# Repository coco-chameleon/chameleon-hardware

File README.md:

# CoCo Chameleon

The CoCo Chameleon is a cartridge for the Tandy TRS-80 Color Computer
line of home computers from the 1980s which emulates other cartridges.
It supports all three versions of the CoCo and should be able to
replicate the computer-facing behavior of nearly any other cartridge.

The primary aim of the project is to emulate ROM cartridges and all
of the common floppy and hard disk controller cartridges from image
files stored on a MicroSD card.

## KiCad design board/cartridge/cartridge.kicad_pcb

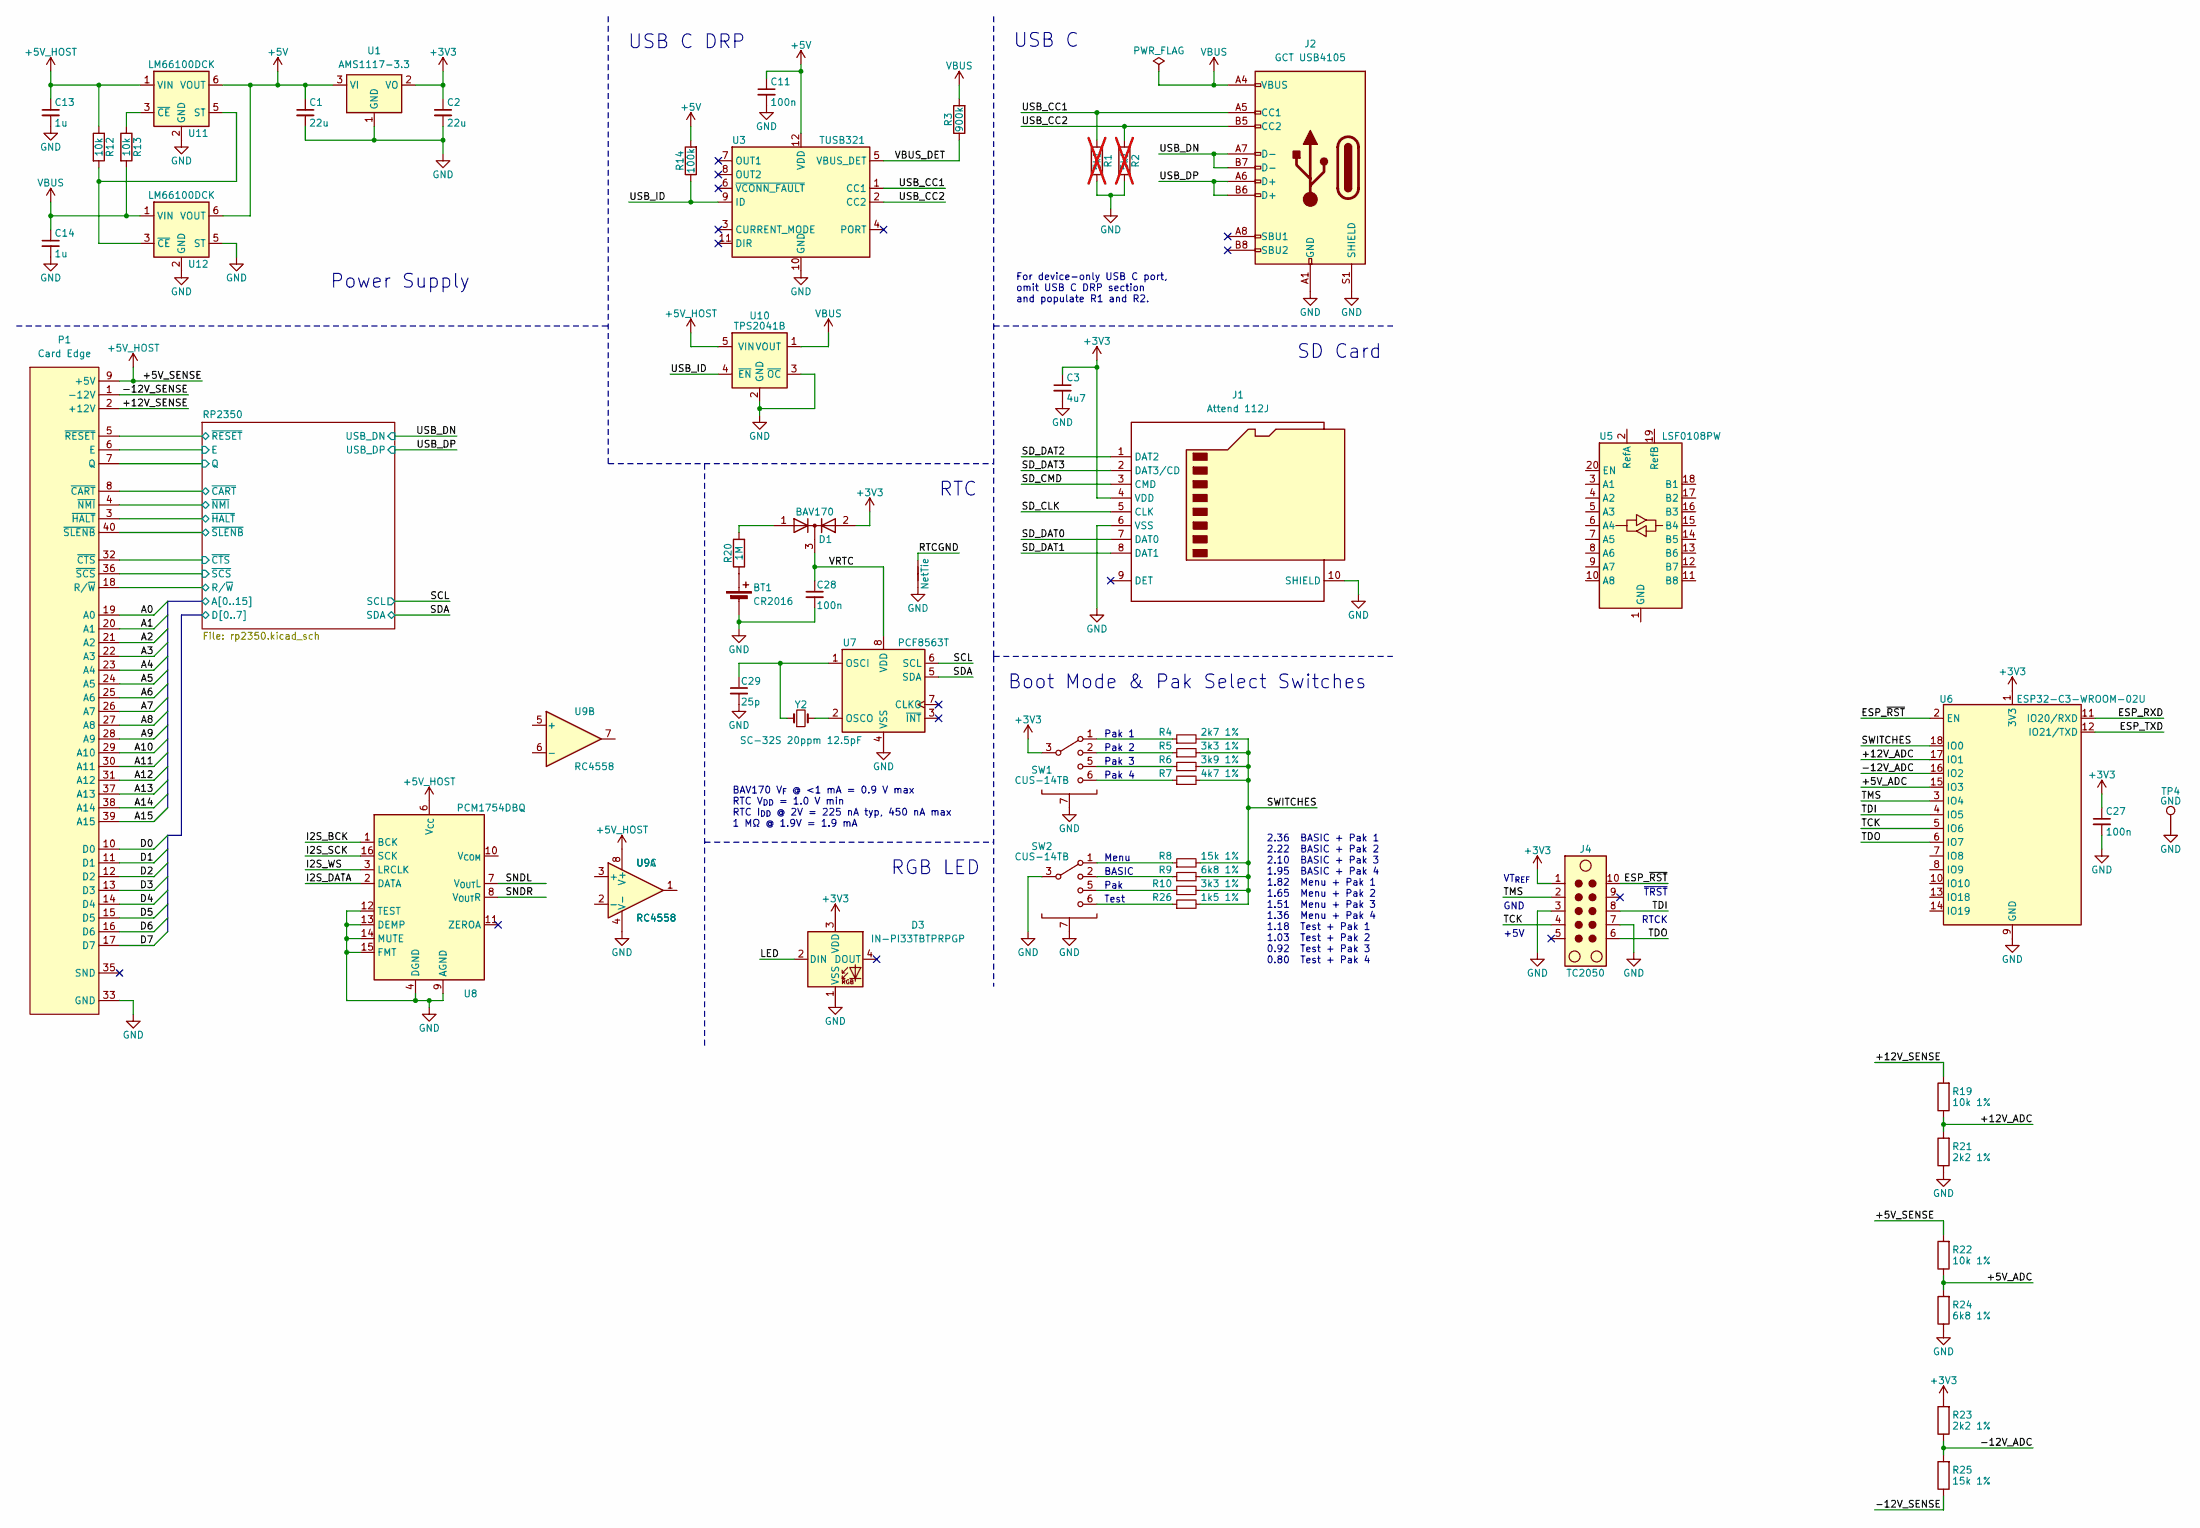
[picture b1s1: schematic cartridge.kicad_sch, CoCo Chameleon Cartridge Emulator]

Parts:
BT1: CR2016; BatteryHolder_Keystone_3026_1x2016
C1, C2: 22u; C_1206_3216Metric
C3: 4u7; C_0603_1608Metric
C11, C27, C28: 100n; C_0603_1608Metric
C13, C14: 1u; C_0603_1608Metric
C29: 25p; C_0603_1608Metric
D1: BAV170; SOT-23; LCSC C109309
D3: IN-PI33TBTPRPGP; LED_1414_3535Metric; LCSC C5259062
J1: Attend 112J; Attend_112J; LCSC C393941
J2: GCT USB4105; GCT_USB4105; LCSC C2894898
J4: TC2050; Tag-Connect_TC2050-IDC-NL_2x05_P1.27mm_Vertical
NT1: NetTie
P1: Card Edge; CoCo_Cart
R1, R2: 5k1; R_0603_1608Metric; not fitted
R3: 900k; R_0603_1608Metric
R4: 2k7 1%; R_0402_1005Metric
R5, R10: 3k3 1%; R_0402_1005Metric
R6: 3k9 1%; R_0402_1005Metric
R7: 4k7 1%; R_0402_1005Metric
R8, R25: 15k 1%; R_0402_1005Metric
R9, R24: 6k8 1%; R_0402_1005Metric
R12, R13: 10k; R_0603_1608Metric
R14: 100k; R_0603_1608Metric
R19, R22: 10k 1%; R_0402_1005Metric
R20: 1M; R_0603_1608Metric
R21, R23: 2k2 1%; R_0402_1005Metric
R26: 1k5 1%; R_0402_1005Metric
SW1, SW2: CUS-14TB; Nidec_CUS-14TB; LCSC C145846
TP4: GND; TestPoint_Pad_4.0x4.0mm
U1: AMS1117-3.3; SOT-223-3_TabPin2; LCSC C6186
U3: TUSB321; Texas_X2QFN-12_1.6x1.6mm_P0.4mm; LCSC C139392
U5: LSF0108PW; TSSOP-20_4.4x6.5mm_P0.65mm; LCSC C190219
U6: ESP32-C3-WROOM-02U
U7: PCF8563T; SOIC-8_3.9x4.9mm_P1.27mm; LCSC C7440
U8: PCM1754DBQ; SSOP-16_3.9x4.9mm_P0.635mm
U9: RC4558; SOIC-8_3.9x4.9mm_P1.27mm
U10: TPS2041B; SOT-23-5; LCSC C51386
U11, U12: LM66100DCK; SOT-363_SC-70-6; LCSC C2869734
Y2: SC-32S 20ppm 12.5pF; Crystal_SMD_3215-2Pin_3.2x1.5mm; LCSC C97606

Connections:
+3V3: C2.1, C3.1, C27.1, D1.2 (A), D3.3 (VDD), J1.4 (VDD), J4.1, R23.2, SW1.3 (COM), SW1.4 (COM), U1.2 (VO), U6.1 (3V3); also elsewhere on the board
+5V: C1.1, C11.1, R14.2, U1.3 (VI), U3.12 (VDD), U11.6 (VOUT), U12.6 (VOUT)
+5V_HOST: C13.1, P1.9 (+5V), R12.1, R22.2, U8.6 (V_{CC}), U9.8 (V+), U10.5 (VIN), U11.1 (VIN)
/+5V_ADC: R22.1, R24.2, U6.15 (IO3)
/+12V_ADC: R19.1, R21.2, U6.17 (IO1)
/+12V_SENSE: P1.2 (+12V), R19.2
/-12V_ADC: R23.1, R25.2, U6.16 (IO2)
/-12V_SENSE: P1.1 (-12V), R25.1
/ESP_RXD: U6.11 (IO20/RXD)
/ESP_TXD: U6.12 (IO21/TXD)
/ESP_~RST: J4.10, U6.2 (EN)
/I2S_BCK: U8.1 (BCK)
/I2S_DATA: U8.2 (DATA)
/I2S_SCK: U8.16 (SCK)
/I2S_WS: U8.3 (LRCLK)
/LED: D3.2 (DIN)
/RP2350/A0: P1.19 (A0); also elsewhere on the board
/RP2350/A1: P1.20 (A1); also elsewhere on the board
/RP2350/A2: P1.21 (A2); also elsewhere on the board
/RP2350/A3: P1.22 (A3); also elsewhere on the board
/RP2350/A4: P1.23 (A4); also elsewhere on the board
/RP2350/A5: P1.24 (A5); also elsewhere on the board
/RP2350/A6: P1.25 (A6); also elsewhere on the board
/RP2350/A7: P1.26 (A7); also elsewhere on the board
/RP2350/A8: P1.27 (A8); also elsewhere on the board
/RP2350/A9: P1.28 (A9); also elsewhere on the board
/RP2350/A10: P1.29 (A10); also elsewhere on the board
/RP2350/A11: P1.30 (A11); also elsewhere on the board
/RP2350/A12: P1.31 (A12); also elsewhere on the board
/RP2350/A13: P1.37 (A13); also elsewhere on the board
/RP2350/A14: P1.38 (A14); also elsewhere on the board
/RP2350/A15: P1.39 (A15); also elsewhere on the board
/RP2350/D0: P1.10 (D0); also elsewhere on the board
/RP2350/D1: P1.11 (D1); also elsewhere on the board
/RP2350/D2: P1.12 (D2); also elsewhere on the board
/RP2350/D3: P1.13 (D3); also elsewhere on the board
/RP2350/D4: P1.14 (D4); also elsewhere on the board
/RP2350/D5: P1.15 (D5); also elsewhere on the board
/RP2350/D6: P1.16 (D6); also elsewhere on the board
/RP2350/D7: P1.17 (D7); also elsewhere on the board
/RP2350/E: P1.6 (E); also elsewhere on the board
/RP2350/Q: P1.7 (Q); also elsewhere on the board
/RP2350/R/~W: P1.18 (R/~W); also elsewhere on the board
/RP2350/~CART: P1.8 (~CART); also elsewhere on the board
/RP2350/~CTS: P1.32 (~CTS); also elsewhere on the board
/RP2350/~HALT: P1.3 (~HALT); also elsewhere on the board
/RP2350/~NMI: P1.4 (~NMI); also elsewhere on the board
/RP2350/~RESET: P1.5 (~RESET); also elsewhere on the board
/RP2350/~SCS: P1.36 (~SCS); also elsewhere on the board
/RP2350/~SLENB: P1.40 (~SLENB); also elsewhere on the board
/SCL: U7.6 (SCL); also elsewhere on the board
/SDA: U7.5 (SDA); also elsewhere on the board
/SD_CLK: J1.5 (CLK)
/SD_CMD: J1.3 (CMD)
/SD_DAT0: J1.7 (DAT0)
/SD_DAT1: J1.8 (DAT1)
/SD_DAT2: J1.1 (DAT2)
/SD_DAT3: J1.2 (DAT3/CD)
/SNDL: U8.7 (V_{OUT}L)
/SNDR: U8.8 (V_{OUT}R)
/SWITCHES: R4.2, R5.2, R6.2, R7.2, R8.2, R9.2, R10.2, R26.2, U6.18 (IO0)
/TCK: J4.4, U6.5 (IO6)
/TDI: J4.8, U6.4 (IO5)
/TDO: J4.6, U6.6 (IO7)
/TMS: J4.2, U6.3 (IO4)
/USB_CC1: J2.A5 (CC1), R1.1, U3.1 (CC1)
/USB_CC2: J2.B5 (CC2), R2.1, U3.2 (CC2)
/USB_DN: J2.A7 (D-), J2.B7 (D-); also elsewhere on the board
/USB_DP: J2.A6 (D+), J2.B6 (D+); also elsewhere on the board
/USB_ID: R14.1, U3.9 (ID), U10.4 (~EN)
/VBUS_DET: R3.1, U3.5 (VBUS_DET)
/VRTC: C28.1, D1.3 (K), U7.8 (VDD)
GND: BT1.2 (-), C1.2, C2.2, C3.2, C11.2, C13.2, C14.2, C27.2, C28.2, C29.2, D3.1 (VSS), J1.6 (VSS), J1.10 (SHIELD), J2.A1 (GND), J2.A12 (GND), J2.B1 (GND), J2.B12 (GND), J2.S1 (SHIELD), J4.3, J4.7, NT1.1, P1.33 (GND), P1.34 (GND), R1.2, R2.2, R21.1, R24.1, SW1.7 (SHIELD), SW2.3 (COM), SW2.4 (COM), SW2.7 (SHIELD), TP4.1, U1.1 (GND), U3.10 (GND), U6.9 (GND), U6.19 (GND), U7.4 (VSS), U8.4 (DGND), U8.9 (AGND), U8.12 (TEST), U8.13 (DEMP), U8.14 (MUTE), U8.15 (FMT), U9.4 (V-), U10.2 (GND), U10.3 (~OC), U11.2 (GND), U12.2 (GND), U12.5 (ST); also elsewhere on the board
unnamed: BT1.1 (+), R20.1
unnamed: D1.1 (A), R20.2
unnamed: R4.1, SW1.1
unnamed: R5.1, SW1.2
unnamed: R8.1, SW2.1
unnamed: R9.1, SW2.2
unnamed: R6.1, SW1.5 (3)
unnamed: R7.1, SW1.6 (4)
unnamed: R10.1, SW2.5 (3)
unnamed: R26.1, SW2.6 (4)
unnamed: C29.1, U7.1 (OSCI), Y2.1
unnamed: U7.2 (OSCO), Y2.2
unnamed: R12.2, U11.5 (ST), U12.3 (~CE)
unnamed: R13.1, U11.3 (~CE)
VBUS: C14.1, J2.A4 (VBUS), J2.A9 (VBUS), J2.B4 (VBUS), J2.B9 (VBUS), R3.2, R13.2, U10.1 (VOUT), U12.1 (VIN)

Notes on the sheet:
SD Card
For device-only USB C port, omit USB C DRP section and populate R1 and R2.
Pak
Pak 3
BASIC
RTC
RTCK
2.36 BASIC + Pak 1 2.22 BASIC + Pak 2 2.10 BASIC + Pak 3 1.95 BASIC + Pak 4 1.82 Menu + Pak 1 1.65 Menu + Pak 2 1.51 Menu + Pak 3 1.36 Menu + Pak 4 1.18 Test + Pak 1 1.03 Test + Pak 2 0.92 Test + Pak 3 0.80 Test + Pak 4
Boot Mode & Pak Select Switches
VT_{REF}
+5V
Power Supply
BAV170 V_{F} @ <1 mA = 0.9 V max RTC V_{DD} = 1.0 V min RTC I_{DD} @ 2V = 225 nA typ, 450 nA max 1 MΩ @ 1.9V = 1.9 mA
USB C DRP
Test
~{TRST}
GND
Pak 4
Pak 1
RGB LED
Menu
Pak 2
USB C

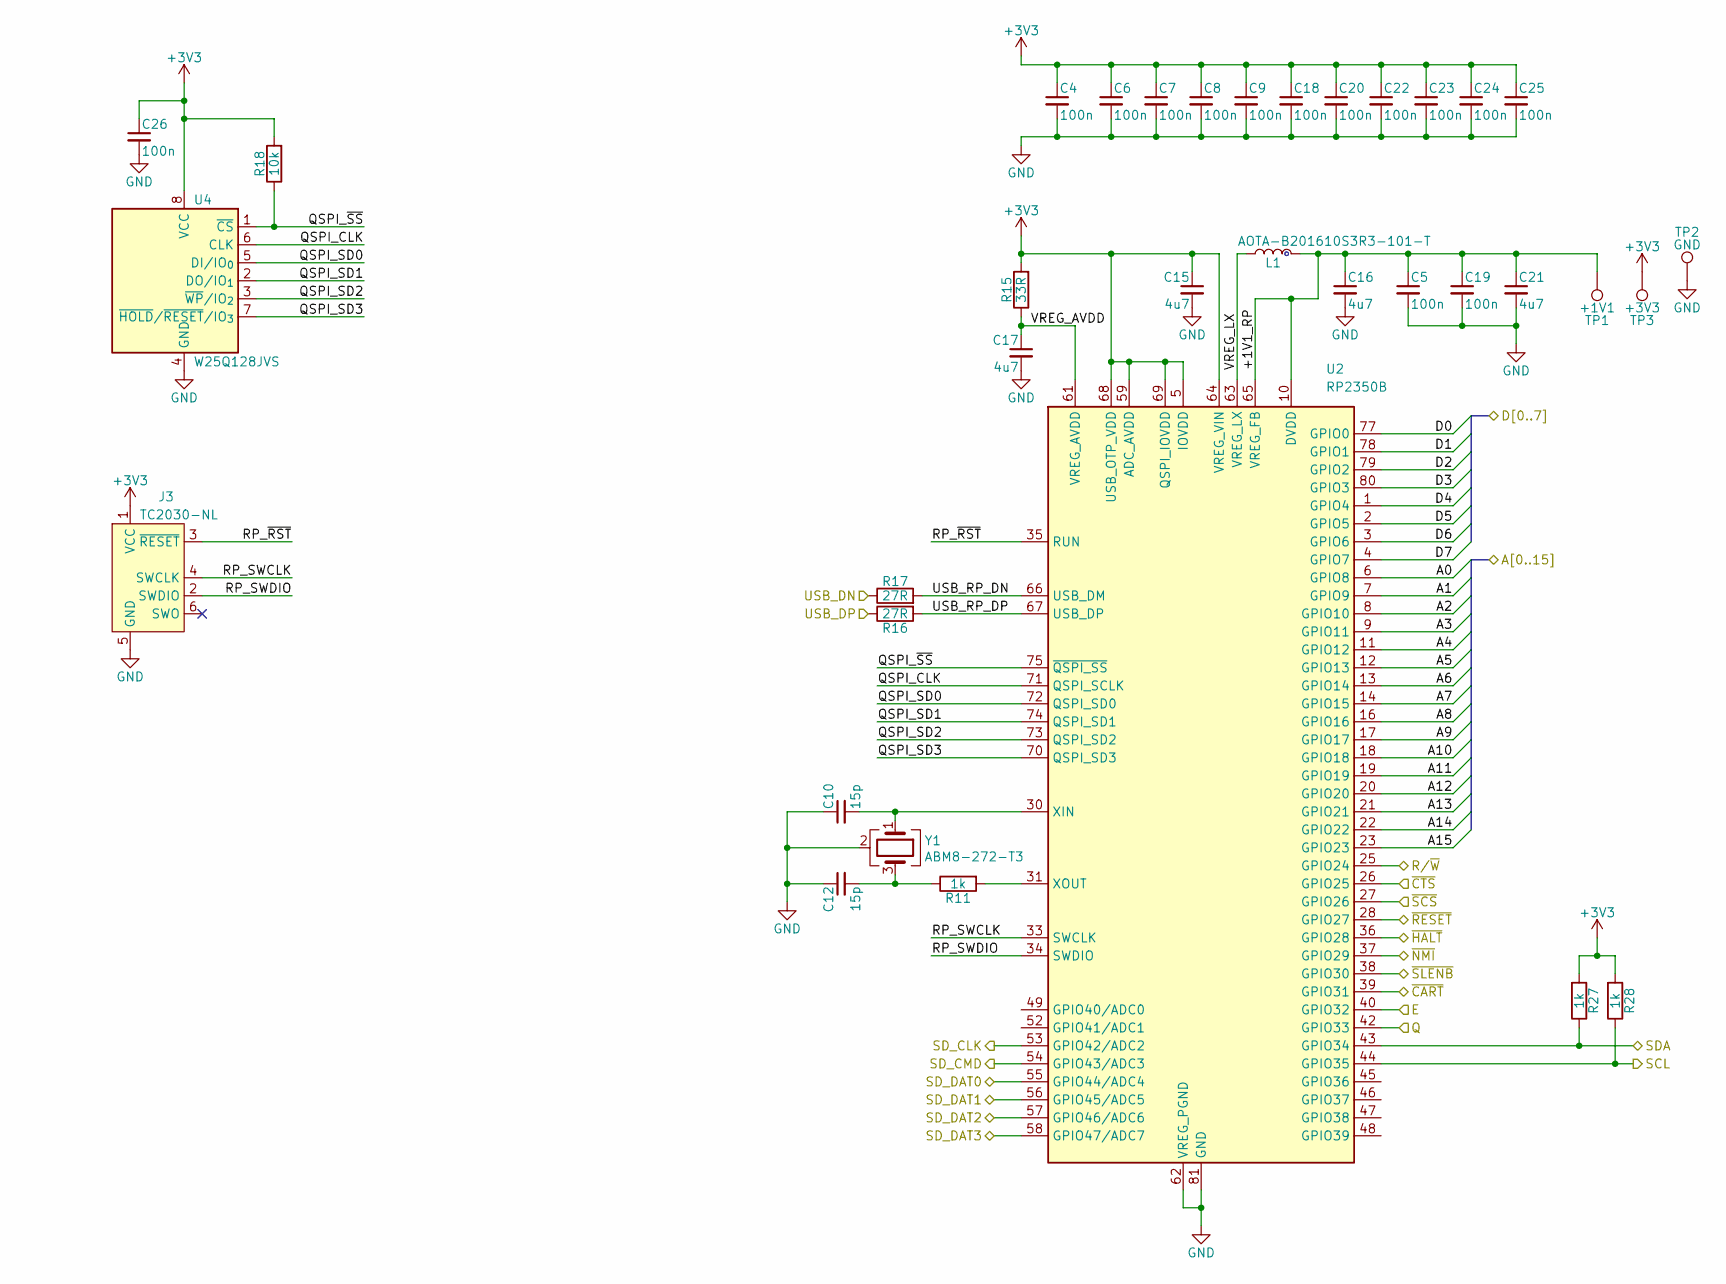
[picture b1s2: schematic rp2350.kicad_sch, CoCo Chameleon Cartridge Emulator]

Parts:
C4, C5, C6, C7, C8, C9, C18, C19, C20, C22, C23, C24, C25, C26: 100n; C_0402_1005Metric
C10, C12: 15p; C_0402_1005Metric
C15, C16: 4u7; C_0402_1005Metric_Pad0.53x0.47mm_Passthrough
C17, C21: 4u7; C_0402_1005Metric
J3: TC2030-NL; Tag-Connect_TC2030-IDC-NL_2x03_P1.27mm_Vertical
L1: AOTA-B201610S3R3-101-T; L_Polarized_2016; LCSC C42411119
R11, R27, R28: 1k; R_0402_1005Metric
R15: 33R; R_0402_1005Metric
R16, R17: 27R; R_0402_1005Metric
R18: 10k; R_0402_1005Metric
TP1: +1V1; TestPoint_Pad_D2.0mm
TP2: GND; TestPoint_Pad_4.0x4.0mm
TP3: +3V3; TestPoint_Pad_D2.0mm
U2: RP2350B; RP2350-QFN-80-1EP_10x10_P0.4mm_EP3.4x3.4mm_ThermalVias; LCSC C42415655
U4: W25Q128JVS; SOIC-8_3.9-5.3x5.3mm_P1.27mm
Y1: ABM8-272-T3; Crystal_SMD_3225-4Pin_3.2x2.5mm; LCSC C20625731

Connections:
+3V3: C4.1, C6.1, C7.1, C8.1, C9.1, C15.1, C18.1, C20.1, C22.1, C23.1, C24.1, C25.1, C26.1, J3.1 (VCC), R15.2, R18.2, R27.2, R28.2, TP3.1, U2.5 (IOVDD), U2.15 (IOVDD), U2.24 (IOVDD), U2.29 (IOVDD), U2.41 (IOVDD), U2.50 (IOVDD), U2.59 (ADC_AVDD), U2.60 (IOVDD), U2.64 (VREG_VIN), U2.68 (USB_OTP_VDD), U2.69 (QSPI_IOVDD), U2.76 (IOVDD), U4.8 (VCC); also elsewhere on the board
/RP2350/+1V1_RP: C5.1, C16.1, C19.1, C21.1, L1.1, TP1.1, U2.10 (DVDD), U2.32 (DVDD), U2.51 (DVDD), U2.65 (VREG_FB)
/RP2350/A0: U2.6 (GPIO8); also elsewhere on the board
/RP2350/A1: U2.7 (GPIO9); also elsewhere on the board
/RP2350/A2: U2.8 (GPIO10); also elsewhere on the board
/RP2350/A3: U2.9 (GPIO11); also elsewhere on the board
/RP2350/A4: U2.11 (GPIO12); also elsewhere on the board
/RP2350/A5: U2.12 (GPIO13); also elsewhere on the board
/RP2350/A6: U2.13 (GPIO14); also elsewhere on the board
/RP2350/A7: U2.14 (GPIO15); also elsewhere on the board
/RP2350/A8: U2.16 (GPIO16); also elsewhere on the board
/RP2350/A9: U2.17 (GPIO17); also elsewhere on the board
/RP2350/A10: U2.18 (GPIO18); also elsewhere on the board
/RP2350/A11: U2.19 (GPIO19); also elsewhere on the board
/RP2350/A12: U2.20 (GPIO20); also elsewhere on the board
/RP2350/A13: U2.21 (GPIO21); also elsewhere on the board
/RP2350/A14: U2.22 (GPIO22); also elsewhere on the board
/RP2350/A15: U2.23 (GPIO23); also elsewhere on the board
/RP2350/D0: U2.77 (GPIO0); also elsewhere on the board
/RP2350/D1: U2.78 (GPIO1); also elsewhere on the board
/RP2350/D2: U2.79 (GPIO2); also elsewhere on the board
/RP2350/D3: U2.80 (GPIO3); also elsewhere on the board
/RP2350/D4: U2.1 (GPIO4); also elsewhere on the board
/RP2350/D5: U2.2 (GPIO5); also elsewhere on the board
/RP2350/D6: U2.3 (GPIO6); also elsewhere on the board
/RP2350/D7: U2.4 (GPIO7); also elsewhere on the board
/RP2350/E: U2.40 (GPIO32); also elsewhere on the board
/RP2350/Q: U2.42 (GPIO33); also elsewhere on the board
/RP2350/QSPI_CLK: U2.71 (QSPI_SCLK), U4.6 (CLK)
/RP2350/QSPI_SD0: U2.72 (QSPI_SD0), U4.5 (DI/IO_{0})
/RP2350/QSPI_SD1: U2.74 (QSPI_SD1), U4.2 (DO/IO_{1})
/RP2350/QSPI_SD2: U2.73 (QSPI_SD2), U4.3 (~WP/IO_{2})
/RP2350/QSPI_SD3: U2.70 (QSPI_SD3), U4.7 (~HOLD/~RESET/IO_{3})
/RP2350/QSPI_~SS: R18.1, U2.75 (~QSPI_SS), U4.1 (~CS)
/RP2350/RP_SWCLK: J3.4 (SWCLK), U2.33 (SWCLK)
/RP2350/RP_SWDIO: J3.2 (SWDIO), U2.34 (SWDIO)
/RP2350/RP_~RST: J3.3 (~RESET), U2.35 (RUN)
/RP2350/R/~W: U2.25 (GPIO24); also elsewhere on the board
/RP2350/SD_CLK: U2.53 (GPIO42/ADC2)
/RP2350/SD_CMD: U2.54 (GPIO43/ADC3)
/RP2350/SD_DAT0: U2.55 (GPIO44/ADC4)
/RP2350/SD_DAT1: U2.56 (GPIO45/ADC5)
/RP2350/SD_DAT2: U2.57 (GPIO46/ADC6)
/RP2350/SD_DAT3: U2.58 (GPIO47/ADC7)
/RP2350/USB_RP_DN: R17.2, U2.66 (USB_DM)
/RP2350/USB_RP_DP: R16.2, U2.67 (USB_DP)
/RP2350/VREG_AVDD: C17.1, R15.1, U2.61 (VREG_AVDD)
/RP2350/VREG_LX: L1.2, U2.63 (VREG_LX)
/RP2350/~CART: U2.39 (GPIO31); also elsewhere on the board
/RP2350/~CTS: U2.26 (GPIO25); also elsewhere on the board
/RP2350/~HALT: U2.36 (GPIO28); also elsewhere on the board
/RP2350/~NMI: U2.37 (GPIO29); also elsewhere on the board
/RP2350/~RESET: U2.28 (GPIO27); also elsewhere on the board
/RP2350/~SCS: U2.27 (GPIO26); also elsewhere on the board
/RP2350/~SLENB: U2.38 (GPIO30); also elsewhere on the board
/SCL: R28.1, U2.44 (GPIO35); also elsewhere on the board
/SDA: R27.1, U2.43 (GPIO34); also elsewhere on the board
/USB_DN: R17.1; also elsewhere on the board
/USB_DP: R16.1; also elsewhere on the board
GND: C4.2, C5.2, C6.2, C7.2, C8.2, C9.2, C10.1, C12.1, C15.2, C16.2, C17.2, C18.2, C19.2, C20.2, C21.2, C22.2, C23.2, C24.2, C25.2, C26.2, J3.5 (GND), TP2.1, U2.62 (VREG_PGND), U2.81 (GND), U4.4 (GND), Y1.2 (G), Y1.4 (G); also elsewhere on the board
unnamed: C12.2, R11.1, Y1.3
unnamed: C10.2, U2.30 (XIN), Y1.1
unnamed: R11.2, U2.31 (XOUT)

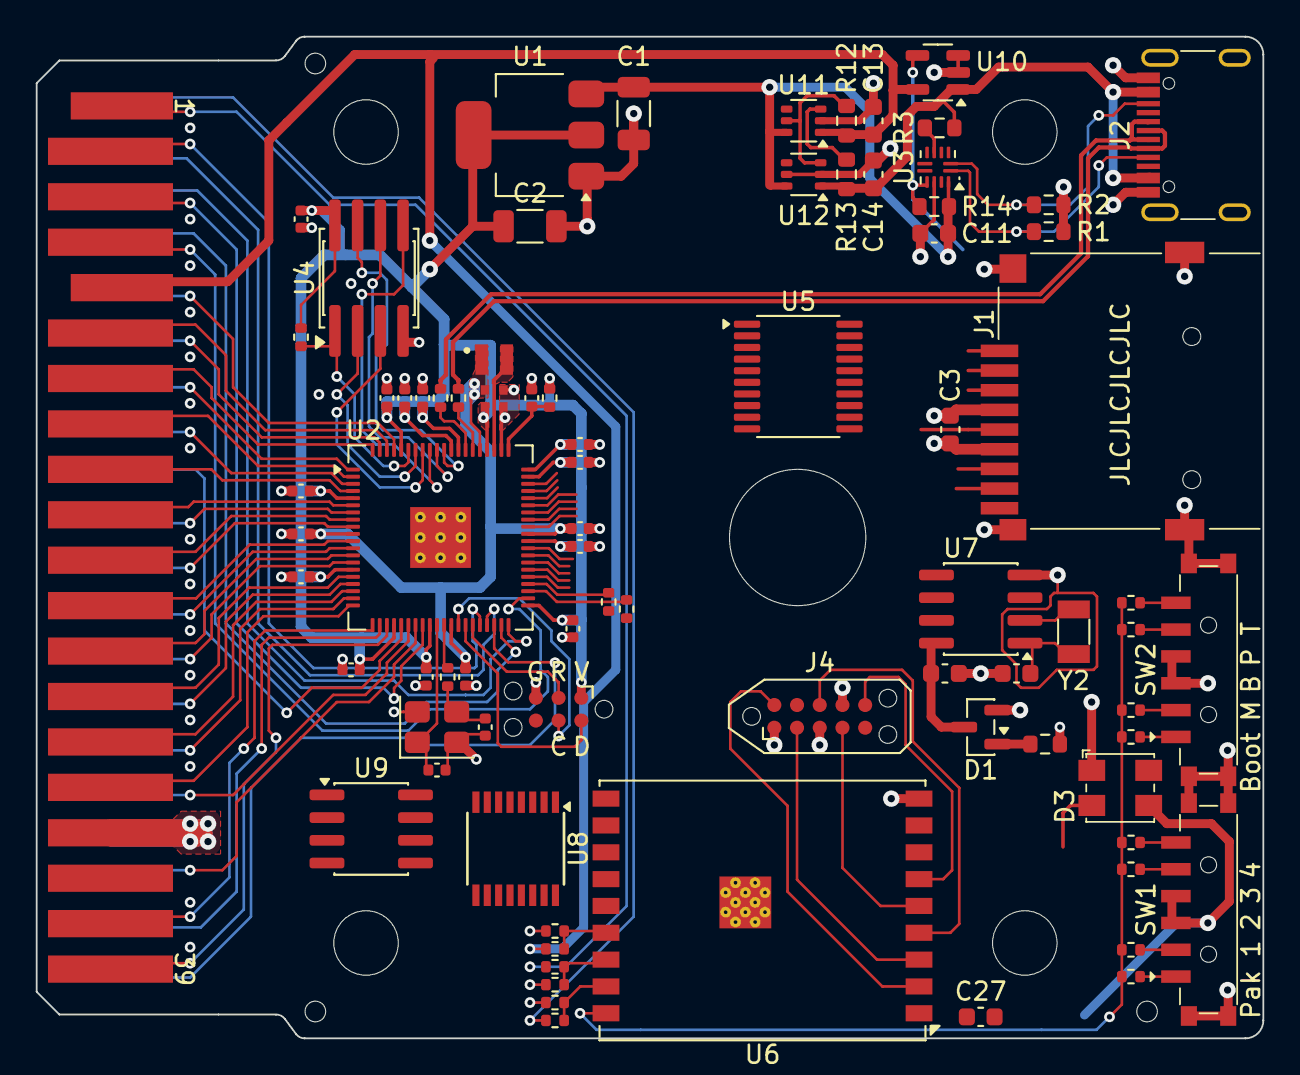
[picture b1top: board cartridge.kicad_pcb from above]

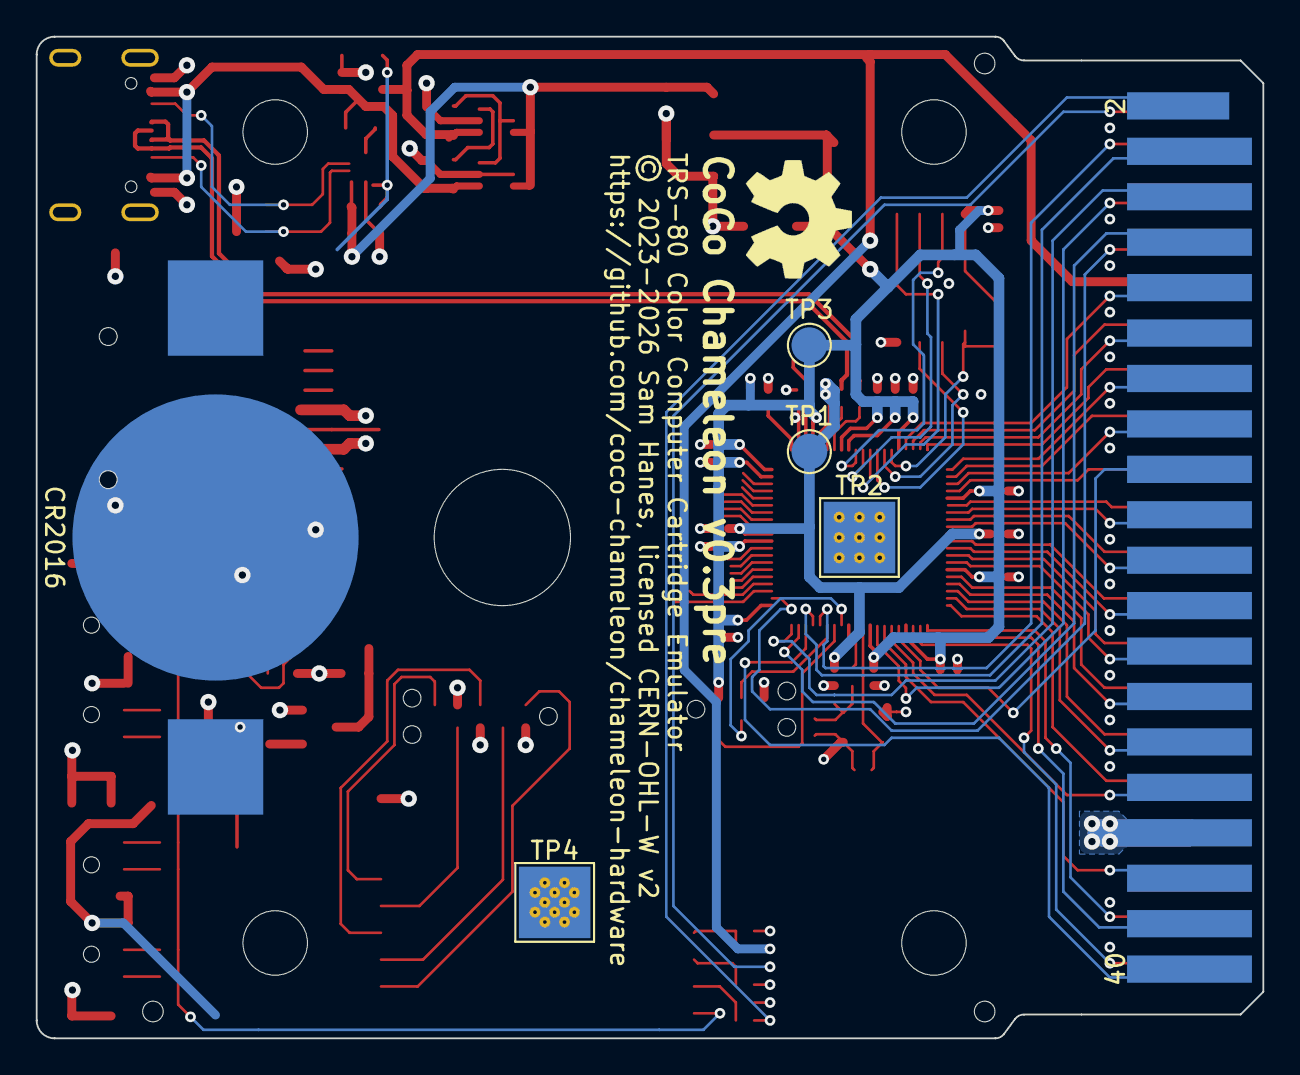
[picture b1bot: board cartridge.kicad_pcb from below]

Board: 4 copper layers, 68.6 x 56.0 mm, 92 parts (6 on the bottom side), 90 nets.

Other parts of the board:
G2: OSHW-Symbol_6.7x6mm_SilkScreen
MH1, MH1#2, MH1#3, MH2: CoCo_MountingHole
MH5: CoCo_ClearanceHole

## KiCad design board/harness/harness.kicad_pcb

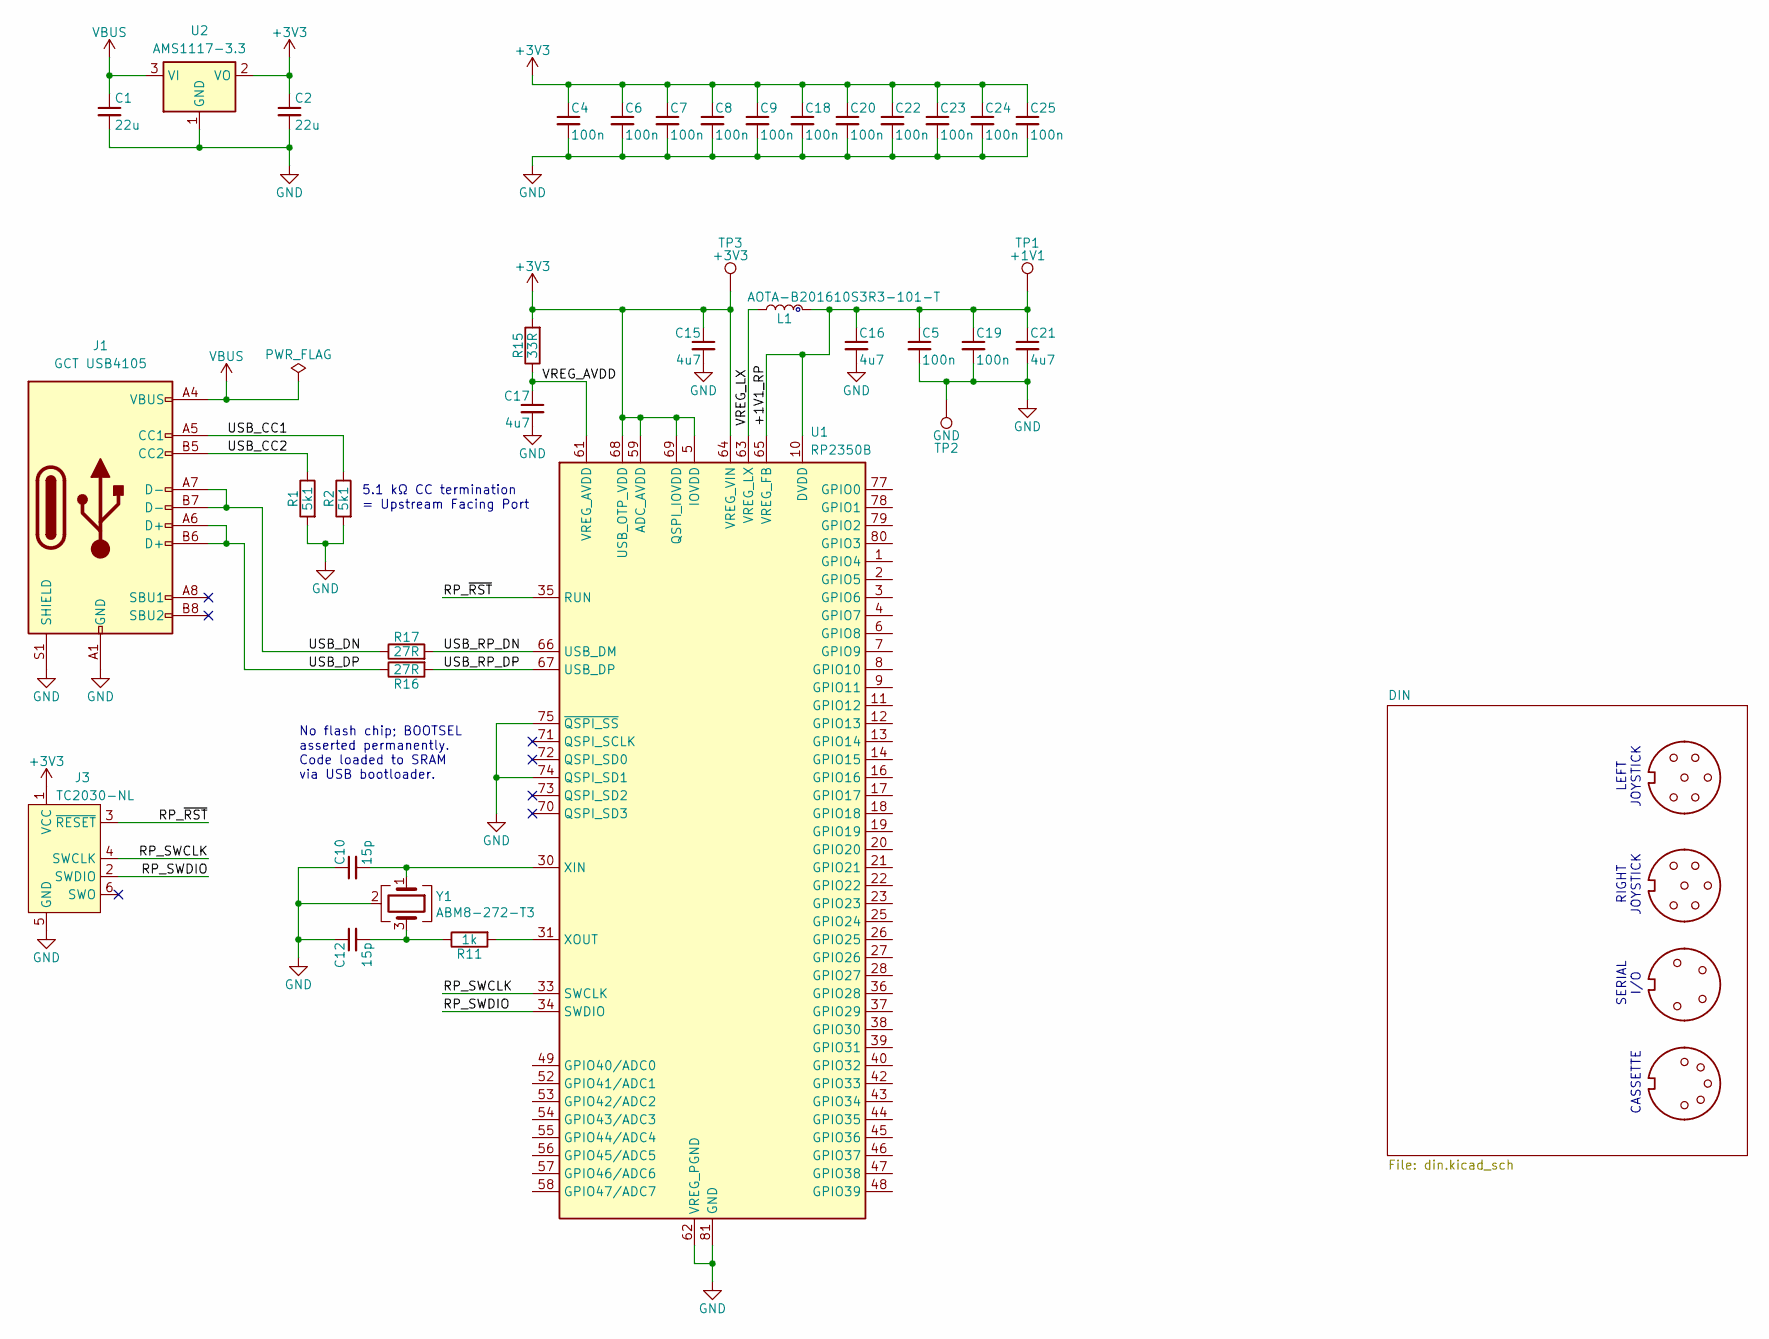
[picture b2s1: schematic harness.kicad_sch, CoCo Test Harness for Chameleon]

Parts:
C1, C2: 22u; C_1206_3216Metric
C4, C5, C6, C7, C8, C9, C18, C19, C20, C22, C23, C24, C25: 100n; C_0402_1005Metric
C10, C12: 15p; C_0402_1005Metric
C15, C16: 4u7; C_0402_1005Metric_Pad0.53x0.47mm_Passthrough
C17, C21: 4u7; C_0402_1005Metric
J1: GCT USB4105; GCT_USB4105; LCSC C2894898
J3: TC2030-NL; Tag-Connect_TC2030-IDC-NL_2x03_P1.27mm_Vertical
L1: AOTA-B201610S3R3-101-T; L_Polarized_2016; LCSC C42411119
R1, R2: 5k1; R_0402_1005Metric
R11: 1k; R_0402_1005Metric
R15: 33R; R_0402_1005Metric
R16, R17: 27R; R_0402_1005Metric
TP1: +1V1; TestPoint_Pad_D2.0mm
TP2: GND; TestPoint_Pad_4.0x4.0mm
TP3: +3V3; TestPoint_Pad_D2.0mm
U1: RP2350B; RP2350-QFN-80-1EP_10x10_P0.4mm_EP3.4x3.4mm_ThermalVias; LCSC C42415655
U2: AMS1117-3.3; SOT-223-3_TabPin2; LCSC C6186
Y1: ABM8-272-T3; Crystal_SMD_3225-4Pin_3.2x2.5mm; LCSC C20625731

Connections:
+3V3: C2.1, C4.1, C6.1, C7.1, C8.1, C9.1, C15.1, C18.1, C20.1, C22.1, C23.1, C24.1, C25.1, J3.1 (VCC), R15.2, TP3.1, U1.5 (IOVDD), U1.15 (IOVDD), U1.24 (IOVDD), U1.29 (IOVDD), U1.41 (IOVDD), U1.50 (IOVDD), U1.59 (ADC_AVDD), U1.60 (IOVDD), U1.64 (VREG_VIN), U1.68 (USB_OTP_VDD), U1.69 (QSPI_IOVDD), U1.76 (IOVDD), U2.2 (VO)
/+1V1_RP: C5.1, C16.1, C19.1, C21.1, L1.1, TP1.1, U1.10 (DVDD), U1.32 (DVDD), U1.51 (DVDD), U1.65 (VREG_FB)
/RP_SWCLK: J3.4 (SWCLK), U1.33 (SWCLK)
/RP_SWDIO: J3.2 (SWDIO), U1.34 (SWDIO)
/RP_~RST: J3.3 (~RESET), U1.35 (RUN)
/USB_CC1: J1.A5 (CC1), R2.1
/USB_CC2: J1.B5 (CC2), R1.1
/USB_DN: J1.A7 (D-), J1.B7 (D-), R17.1
/USB_DP: J1.A6 (D+), J1.B6 (D+), R16.1
/USB_RP_DN: R17.2, U1.66 (USB_DM)
/USB_RP_DP: R16.2, U1.67 (USB_DP)
/VREG_AVDD: C17.1, R15.1, U1.61 (VREG_AVDD)
/VREG_LX: L1.2, U1.63 (VREG_LX)
GND: C1.2, C2.2, C4.2, C5.2, C6.2, C7.2, C8.2, C9.2, C10.1, C12.1, C15.2, C16.2, C17.2, C18.2, C19.2, C20.2, C21.2, C22.2, C23.2, C24.2, C25.2, J1.A1 (GND), J1.A12 (GND), J1.B1 (GND), J1.B12 (GND), J1.S1 (SHIELD), J3.5 (GND), R1.2, R2.2, TP2.1, U1.62 (VREG_PGND), U1.74 (QSPI_SD1), U1.75 (~QSPI_SS), U1.81 (GND), U2.1 (GND), Y1.2 (G), Y1.4 (G)
unnamed: C12.2, R11.1, Y1.3
unnamed: C10.2, U1.30 (XIN), Y1.1
unnamed: R11.2, U1.31 (XOUT)
VBUS: C1.1, J1.A4 (VBUS), J1.A9 (VBUS), J1.B4 (VBUS), J1.B9 (VBUS), U2.3 (VI)

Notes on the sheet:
RIGHT JOYSTICK
No flash chip; BOOTSEL asserted permanently. Code loaded to SRAM via USB bootloader.
5.1 kΩ CC termination = Upstream Facing Port
CASSETTE
LEFT JOYSTICK
SERIAL I/O

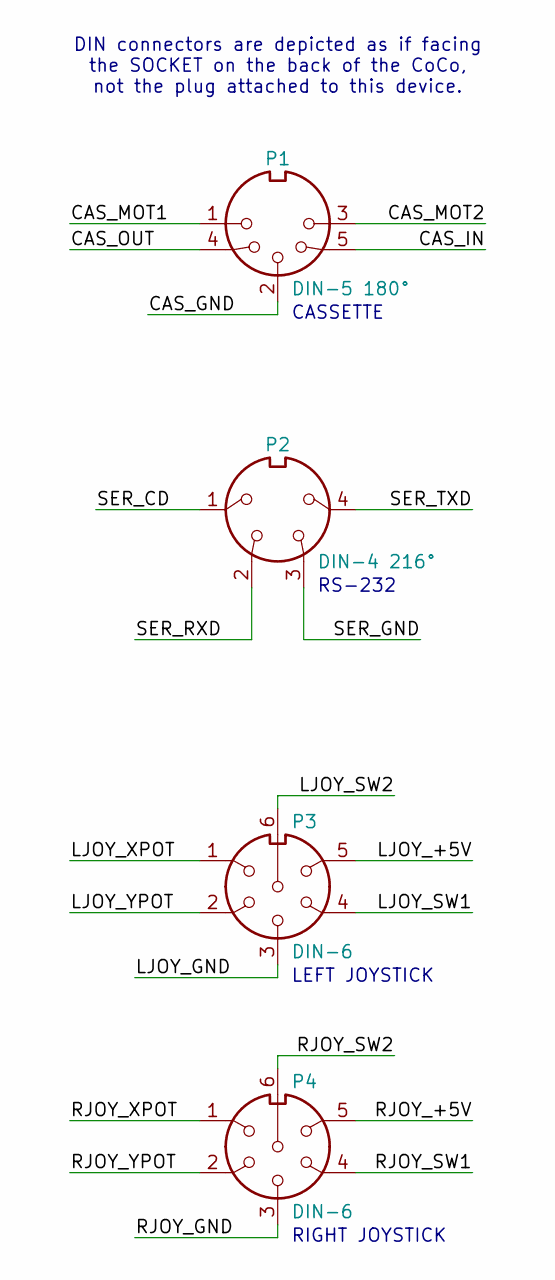
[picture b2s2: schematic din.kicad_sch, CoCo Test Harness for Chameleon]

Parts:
P1: DIN-5 180°; PinHeader_1x05_P2.00mm_Vertical
P2: DIN-4 216°; PinHeader_1x04_P2.00mm_Vertical
P3, P4: DIN-6; PinHeader_1x06_P2.00mm_Vertical

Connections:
/DIN/CAS_GND: P1.2
/DIN/CAS_IN: P1.5
/DIN/CAS_MOT1: P1.1
/DIN/CAS_MOT2: P1.3
/DIN/CAS_OUT: P1.4
/DIN/LJOY_+5V: P3.5
/DIN/LJOY_GND: P3.3
/DIN/LJOY_SW1: P3.4
/DIN/LJOY_SW2: P3.6
/DIN/LJOY_XPOT: P3.1
/DIN/LJOY_YPOT: P3.2
/DIN/RJOY_+5V: P4.5
/DIN/RJOY_GND: P4.3
/DIN/RJOY_SW1: P4.4
/DIN/RJOY_SW2: P4.6
/DIN/RJOY_XPOT: P4.1
/DIN/RJOY_YPOT: P4.2
/DIN/SER_CD: P2.1
/DIN/SER_GND: P2.3
/DIN/SER_RXD: P2.2
/DIN/SER_TXD: P2.4

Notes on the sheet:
LEFT JOYSTICK
DIN connectors are depicted as if facing the SOCKET on the back of the CoCo, not the plug attached to this device.
CASSETTE
RIGHT JOYSTICK
RS-232

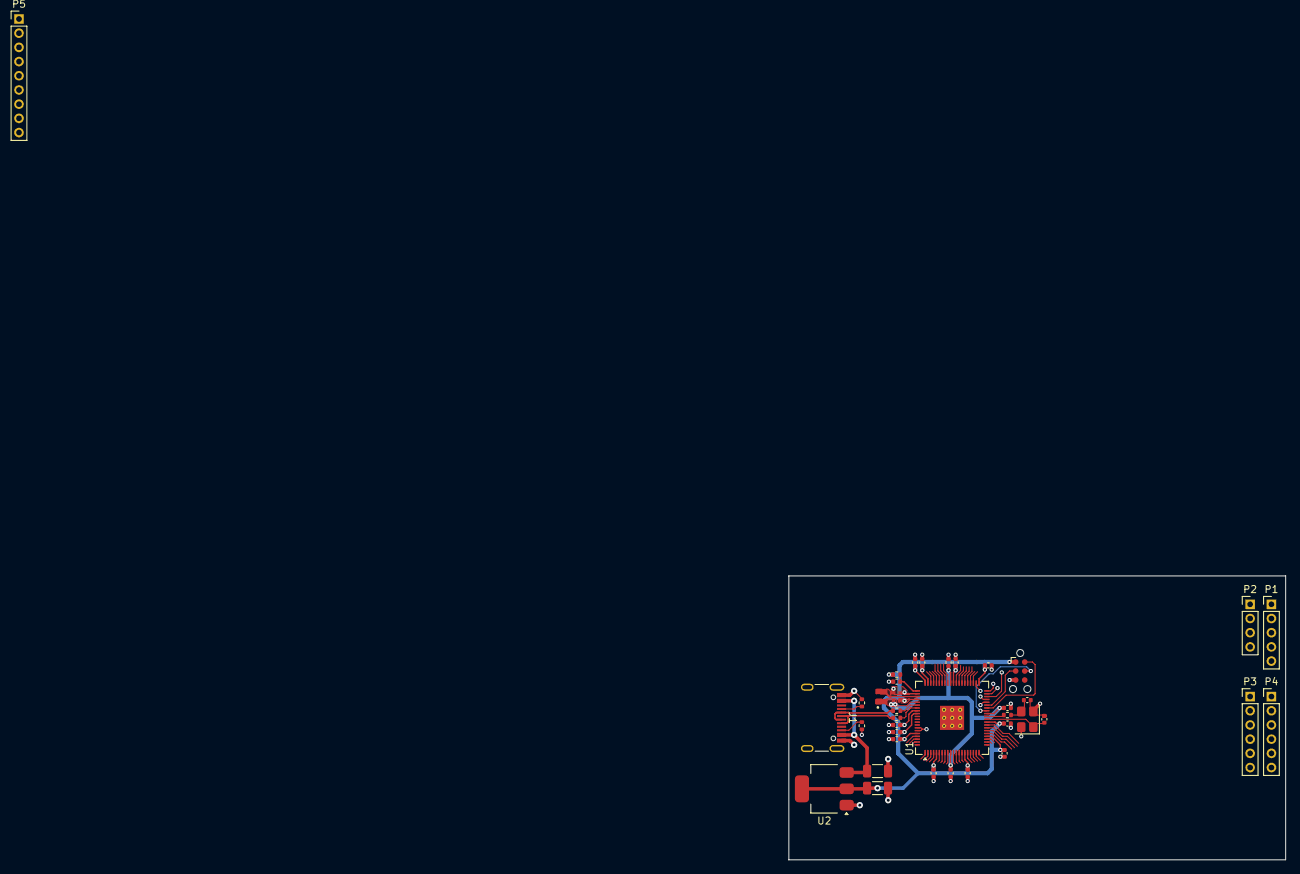
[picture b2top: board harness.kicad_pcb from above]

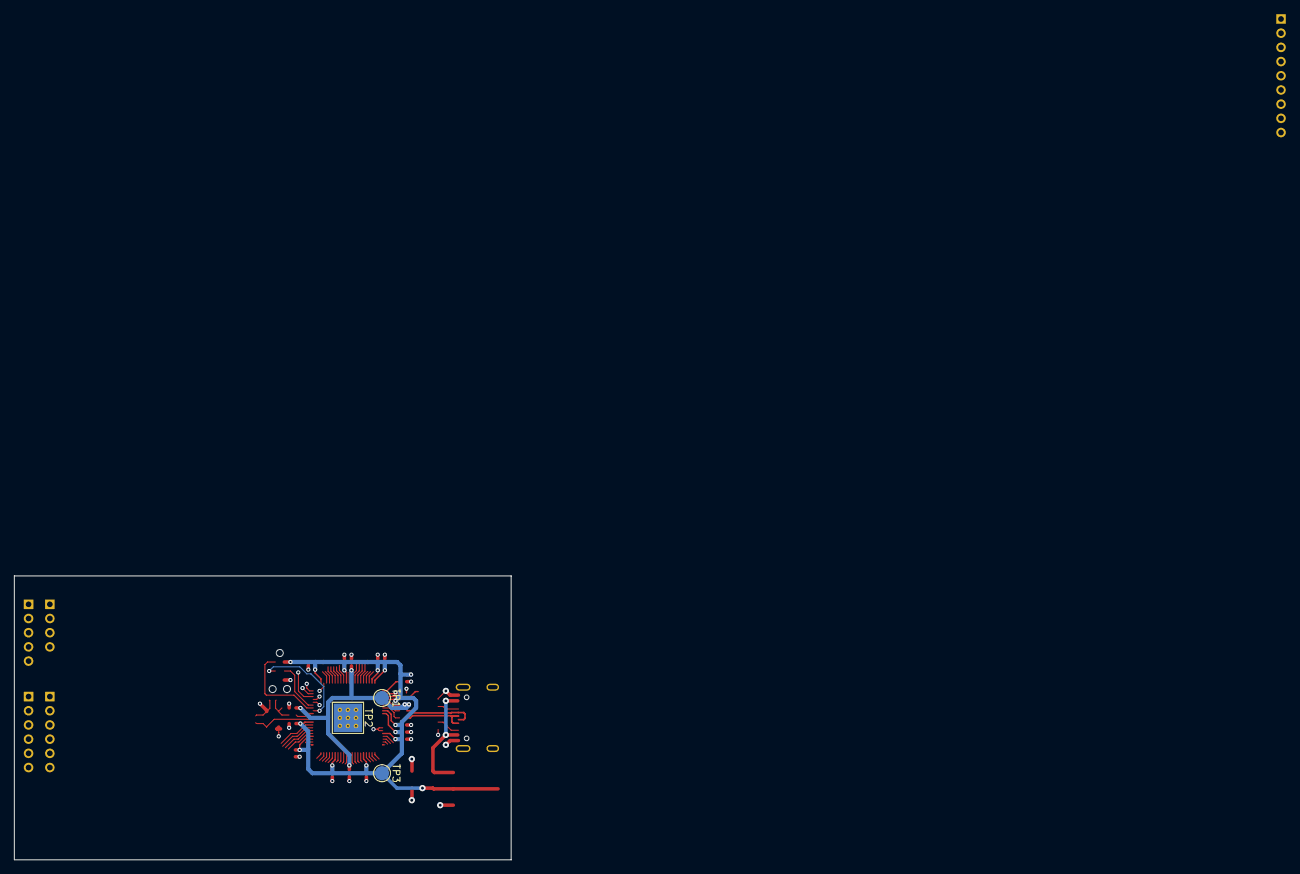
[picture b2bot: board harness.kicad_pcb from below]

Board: 4 copper layers, 70.0 x 40.0 mm, 41 parts (3 on the bottom side), 18 nets.

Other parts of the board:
P5: USB_C_Plug_USB2.0; PinHeader_1x09_P2.00mm_Vertical

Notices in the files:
board/cartridge/cartridge.kicad_pcb:
© 2023-2026 Sam Hanes, licensed CERN-OHL-W v2
board/coco-wedge/coco-wedge.kicad_pcb:
© 2023 Sam Hanes, licensed under CERN-OHL-W v2
board/harness/din.kicad_sch:
© 2026 Sam Hanes, licensed CERN-OHL-W v2
